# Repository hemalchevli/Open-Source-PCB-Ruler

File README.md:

Open-Source-PCB-Ruler
=====================

PCB ruler with different foot prints ,SMD proto-typing area, tables, various AWG size holes and inches and cm scale.
<br>
CC-BY-SA https://creativecommons.org/licenses/by-sa/3.0/
<br>
Suggestions for footprints
<http://black-electronics.com/blog/open-source-pcb-ruler/>
<br>
<br>

<br>

<br><br>
3D views generated from <http://mayhewlabs.com/3dpcb>
<br>
The PCB is designed in CadSoft Eagle.

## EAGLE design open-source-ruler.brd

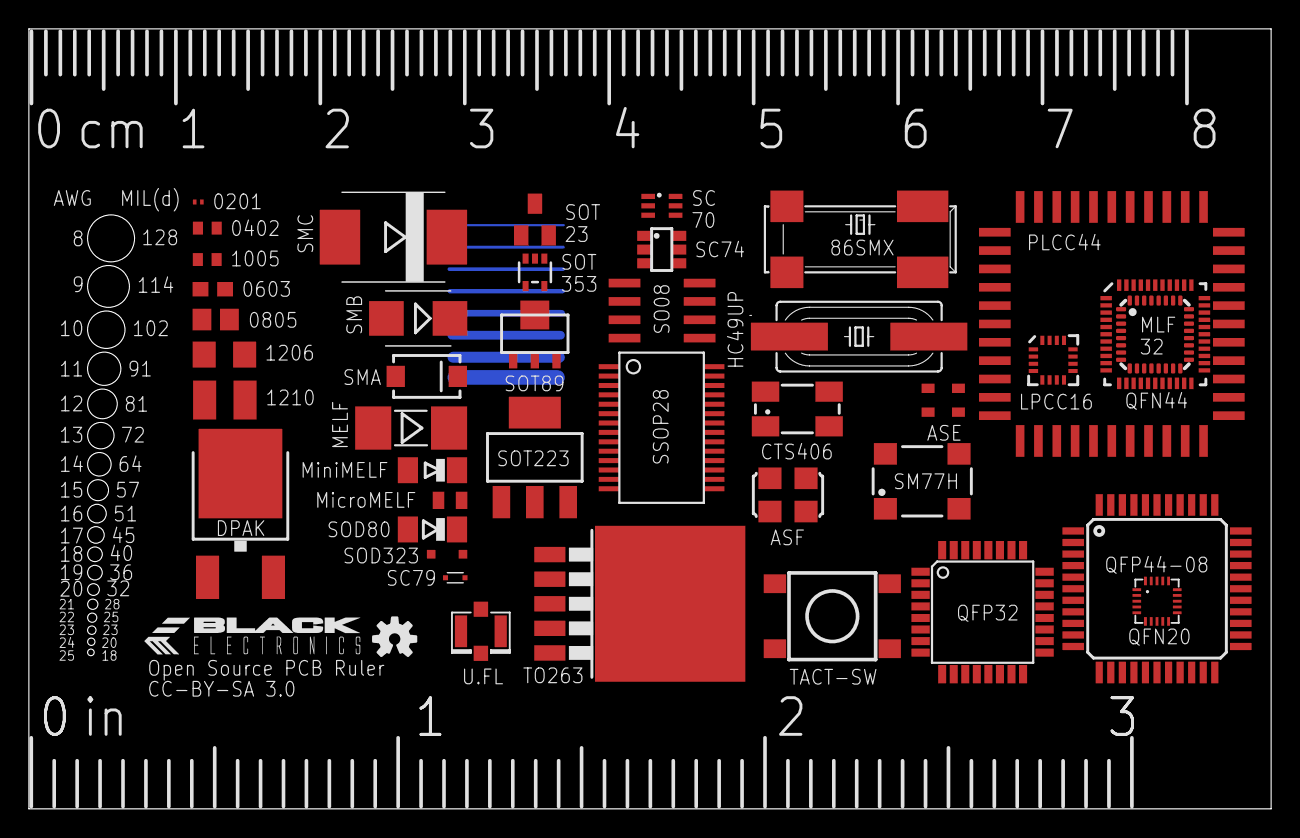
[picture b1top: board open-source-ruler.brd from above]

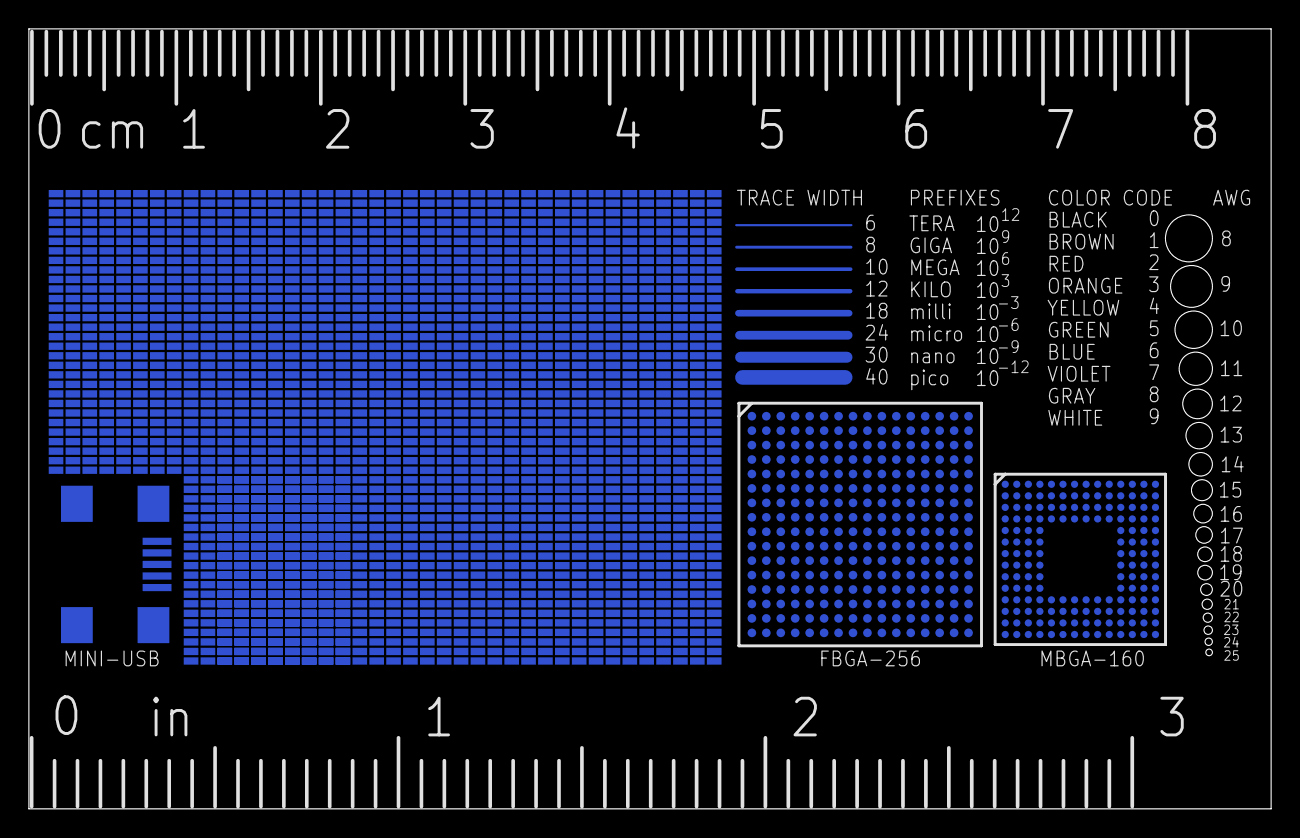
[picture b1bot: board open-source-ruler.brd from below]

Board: 2 copper layers, 86.0 x 54.0 mm, 66 parts (23 on the bottom side), 14 nets.

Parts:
0201: C0201
0402: C0402
0603: C0603
0805: C0805
1005: C1005
1206: C1206
1210: C1210
D1: MICROMELF-R
D2: SOD323-R
D3: SOD80C
D4: SMA-DIODE
D5: SMB
D6: SMC
D7: MELF-MLL41
D8: MINIMELF
IC1: LT1007CS8; SO08
IC2: FT232RLSSOP; SSOP28DB
IC3: MDC3105DMT1; SC-74
IC4: XMEGA16A4A; TQFP44
IC5: LFXP20E_XXF256; FPBGA_256
IC6: PLCC44
IC7: ADSP_BF531; MBGA_160
IC8: SOT223
IC9: TO263-5
Q1: SOT23
Q2: HC49UP
Q3: 86SMX
Q4: ASF1; ASF
Q5: CTS406
Q6: SOT89
QFN20: QFN-20-0.4MM
QG1: SM77H
S1: SWITCH-MOMENTARY-2; TACTILE_SWITCH_TALL
SC79: SC79_INFINEON
U1: V_REG_317DPACK; V-REG_DPACK
U2: ATMEGA168; TQFP32-08
U3: ATMEGA168MLF; MLF32
U4: 7432SE; SOT353
U$1: OSHW-LOGOS; OSHW-LOGO-S
U$2: ADM1087SC-70; SC-70
U$3: ASE
U$4, U$6, U$7, U$8, U$9, U$10, U$11, U$12, U$13, U$14, U$15, U$16, U$17, U$18, U$19, U$20, U$21, U$22, U$23, U$24: PADS
U$5: ATMEGA32U4QFN2; QFN-44-NOPAD
U$25: HMC5883LSMD; 16LPCC
U$26: U.FL
U$27: LOGO_SMALL
X1: MINI-USB-UX60A-MB-5ST; UX60A-MB-5ST

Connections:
GND: IC4.8, IC5.A1, IC5.A16, IC5.F6, IC5.F11, IC5.G7, IC5.G8, IC5.G9, IC5.G10, IC5.H7, IC5.H8, IC5.H9, IC5.H10, IC5.J7, IC5.J8, IC5.J9, IC5.J10, IC5.K7, IC5.K8, IC5.K9, IC5.K10, IC5.L6, IC5.L11, IC5.T1, IC5.T16, IC6.22, IC7.A10, IC7.A14, IC7.B11, IC7.C4, IC7.C5, IC7.C11, IC7.D4, IC7.D7, IC7.D8, IC7.D10, IC7.D11, IC7.F4, IC7.F11, IC7.G11, IC7.H4, IC7.H11, IC7.K4, IC7.K11, IC7.L5, IC7.L6, IC7.L8, IC7.L10, IC7.M10, IC7.P14, IC9.3, IC9.6, Q4.2, QG1.2, U$3.2
VCC: IC2.20, IC4.9, IC5.D4, IC5.D13, IC5.E5, IC5.E12, IC5.M5, IC5.M12, IC5.N4, IC5.N13, IC6.44, Q4.4, QG1.4
VCCAUX: IC5.E4, IC5.E13, IC5.M4, IC5.M13
VCCIO0: IC5.F7, IC5.F8
VCCIO1: IC5.F9, IC5.F10
VCCIO2: IC5.G11, IC5.H11
VCCIO3: IC5.J11, IC5.K11
VCCIO4: IC5.L9, IC5.L10
VCCIO5: IC5.L7, IC5.L8
VCCIO6: IC5.J6, IC5.K6
VCCIO7: IC5.G6, IC5.H6
VDD_EXT: IC7.A1, IC7.C7, IC7.C12, IC7.D5, IC7.D9, IC7.F12, IC7.G4, IC7.J4, IC7.J12, IC7.L7, IC7.L11, IC7.P1
VDD_INT: IC7.D6, IC7.E4, IC7.E11, IC7.J11, IC7.L4, IC7.L9
VROUT: IC7.A13, IC7.B12

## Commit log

2013-11-22 added license
2013-11-22 link to blog post
2013-11-27 Added scales
2013-12-02 modified readme
2013-12-10 Added prototype area
2013-12-12 +trace,colour,few FPs
2013-12-12 Ready for release
2013-12-13 Ready to prototype
2013-12-15 Fixed Issues #1-#4
2013-12-15 3D view
2013-12-15 Added img & links
2013-12-15 description edit
2013-12-17 Added notice
2014-03-09 Fixed #5-#11 issues
2014-03-09 Adding gerbers files
2014-03-09 New snapshots
2014-03-09 changed pics
2017-05-24 fixed image links in the readme

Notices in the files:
open-source-ruler.brd:
CC-BY-SA 3.0
parts and their libraries:
SparkFun: Licensing: CC v3.0 Share-Alike You are welcome to use this library for commercial purposes.
